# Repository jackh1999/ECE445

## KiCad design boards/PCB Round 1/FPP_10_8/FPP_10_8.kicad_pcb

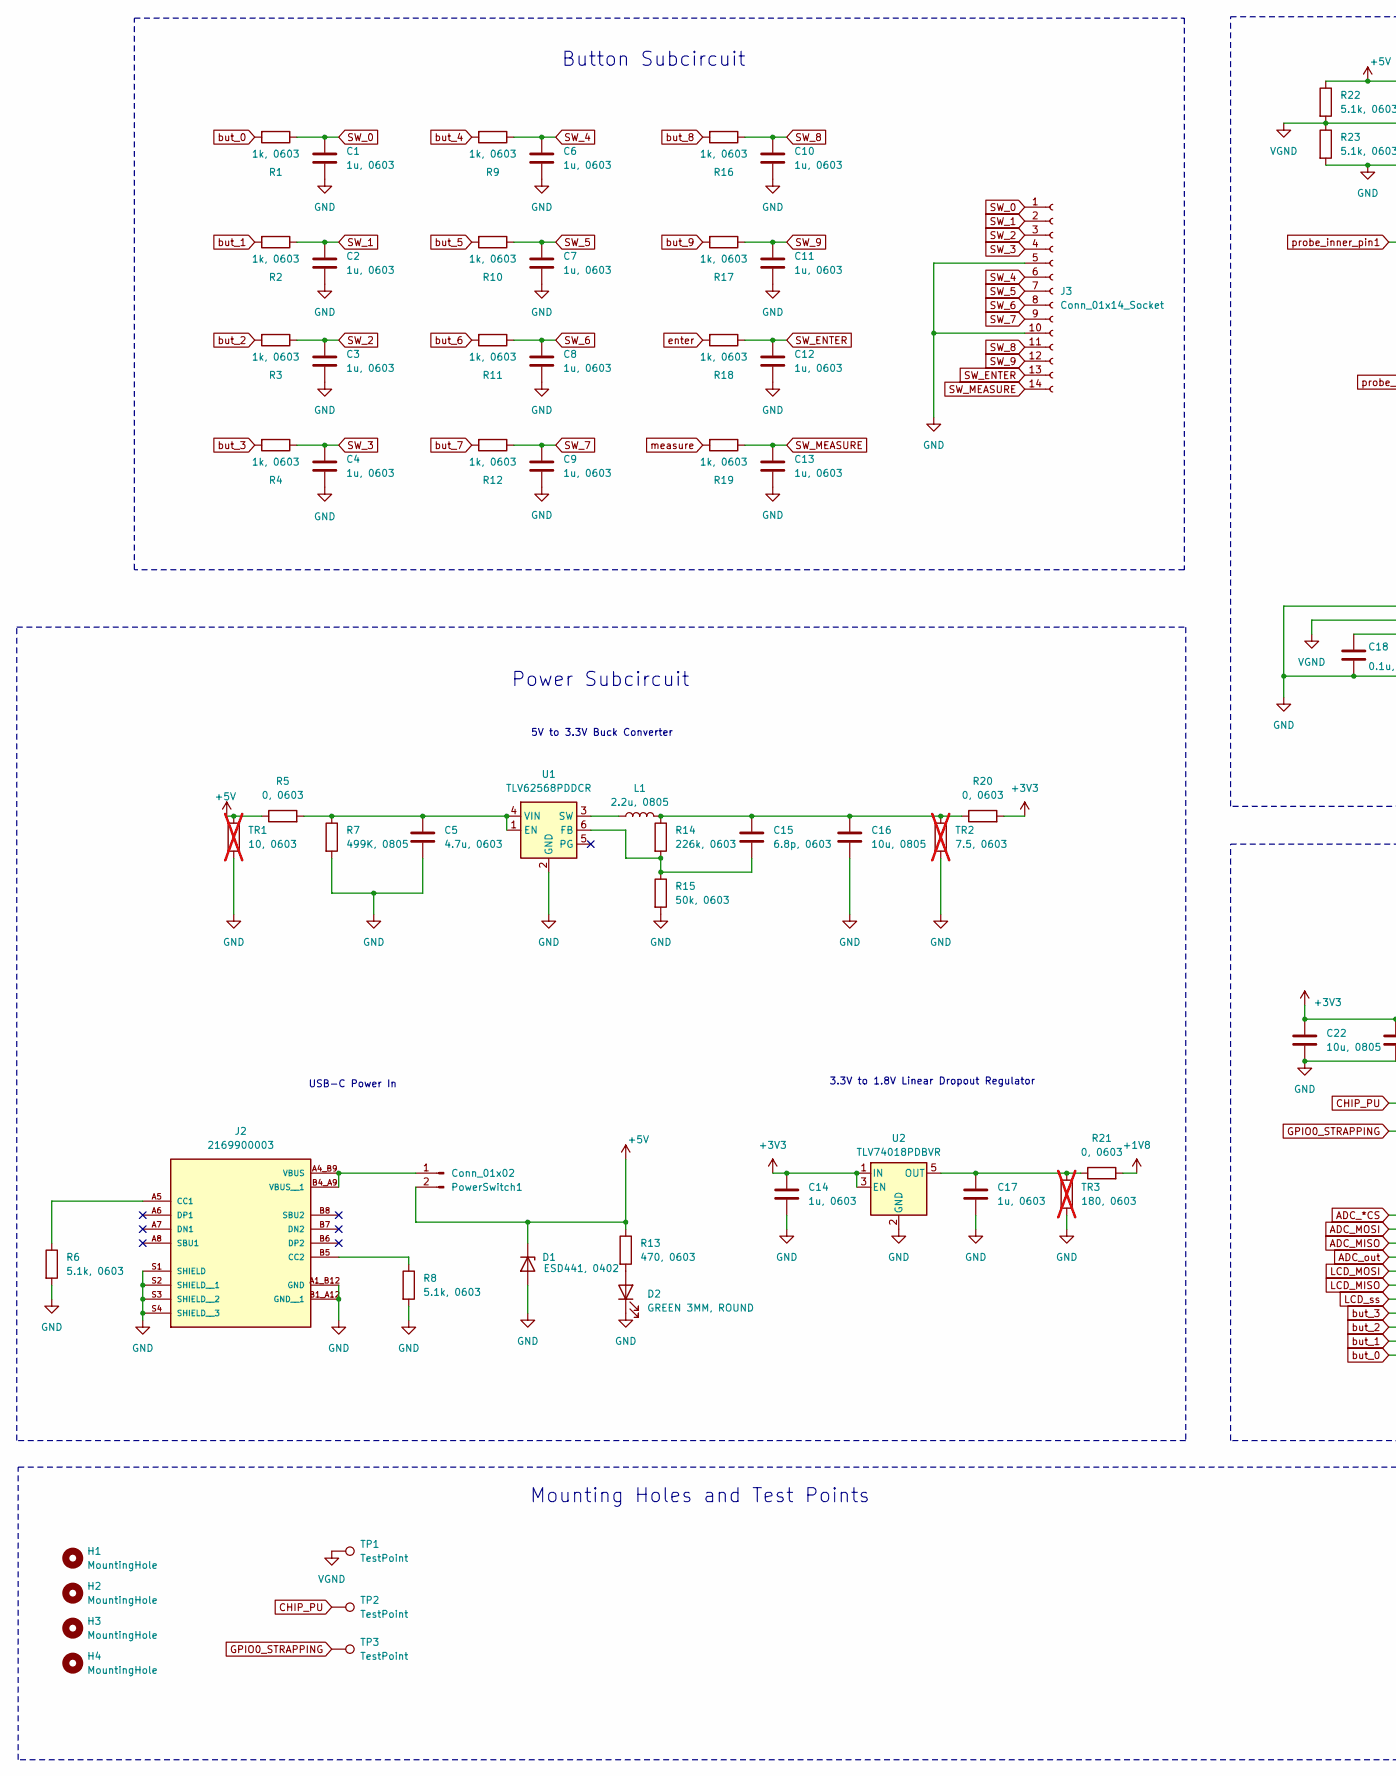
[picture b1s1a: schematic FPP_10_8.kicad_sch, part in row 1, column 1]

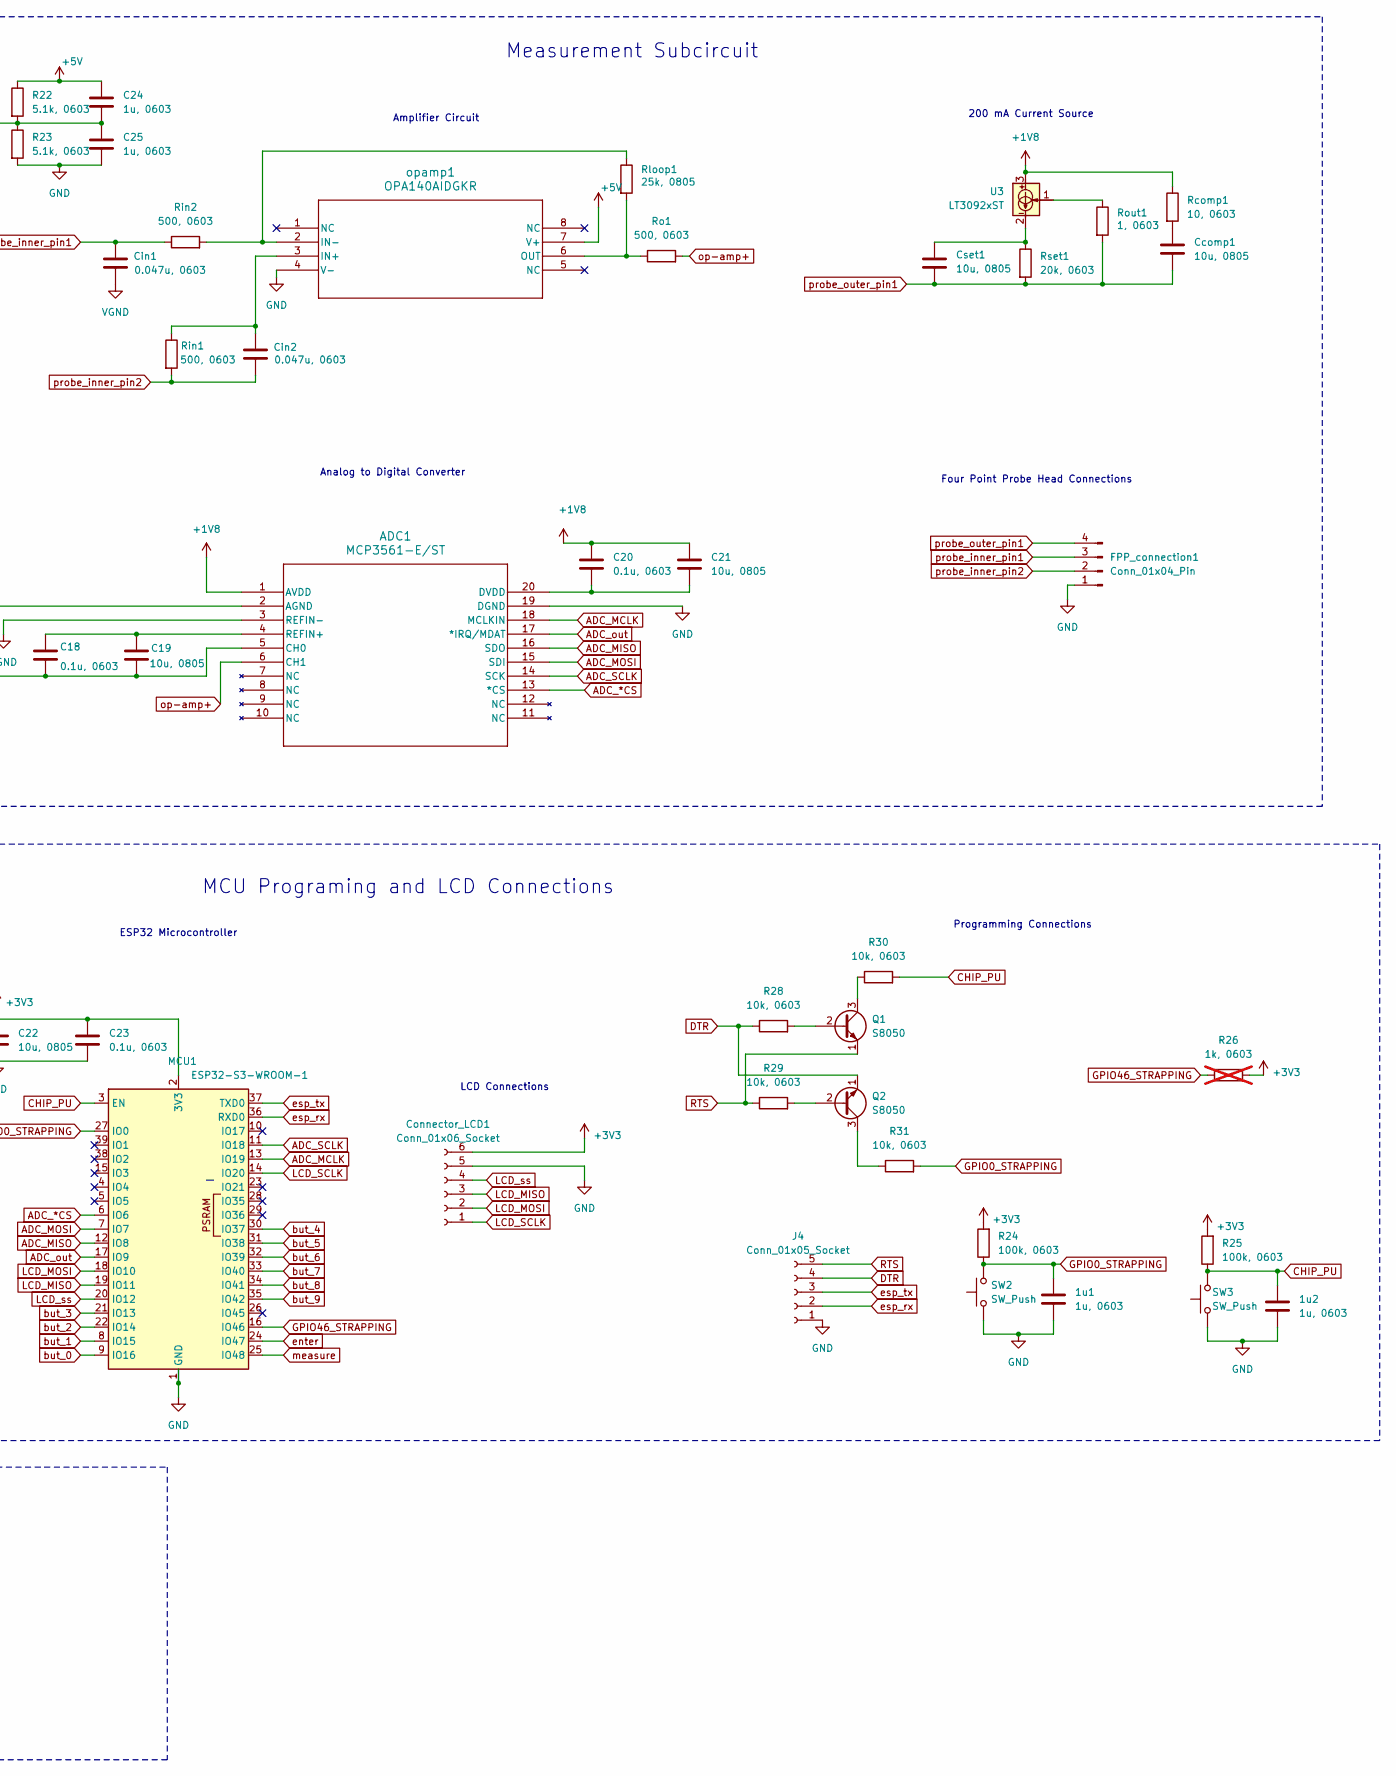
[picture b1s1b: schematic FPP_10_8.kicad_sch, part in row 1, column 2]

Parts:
1u1, 1u2: 1u, 0603; R_0603_1608Metric_Pad0.98x0.95mm_HandSolder
ADC1: MCP3561-E/ST; TSSOP-20_4.4x6.5mm_P0.65mm
C1, C2, C3, C4, C6, C7, C8, C9, C10, C11, C12, C13, C14, C17, C24, C25: 1u, 0603; R_0603_1608Metric_Pad0.98x0.95mm_HandSolder
C5: 4.7u, 0603; R_0603_1608Metric_Pad0.98x0.95mm_HandSolder
C15: 6.8p, 0603; R_0603_1608Metric_Pad0.98x0.95mm_HandSolder
C16, C19, C21, C22: 10u, 0805; R_0805_2012Metric_Pad1.20x1.40mm_HandSolder
C18, C20, C23: 0.1u, 0603; R_0603_1608Metric_Pad0.98x0.95mm_HandSolder
Ccomp1: 10u, 0805; R_0805_2012Metric_Pad1.20x1.40mm_HandSolder
Cin1, Cin2: 0.047u, 0603; R_0603_1608Metric_Pad0.98x0.95mm_HandSolder
Connector_LCD1: Conn_01x06_Socket; PinSocket_1x06_P2.54mm_Vertical
Cset1: 10u, 0805; R_0805_2012Metric_Pad1.20x1.40mm_HandSolder
D1: ESD441, 0402; R_0402_1005Metric_Pad0.72x0.64mm_HandSolder
D2: GREEN 3MM, ROUND; WL-TMRC_3MM
FPP_connection1: Conn_01x04_Pin; PinHeader_1x04_P2.54mm_Vertical
H1, H2, H3, H4: MountingHole; MountingHole_4.3mm_M4
J2: 2169900003; MOLEX_2169900003; PARTREV A1
J3: Conn_01x14_Socket; PinSocket_2x07_P2.54mm_Vertical
J4: Conn_01x05_Socket; PinSocket_1x05_P2.54mm_Vertical
L1: 2.2u, 0805; R_0805_2012Metric_Pad1.20x1.40mm_HandSolder
MCU1: ESP32-S3-WROOM-1
PowerSwitch1: Conn_01x02; Molex_KK-254_AE-6410-02A_1x02_P2.54mm_Vertical
Q1, Q2: S8050; SOT-23-3
R1, R2, R3, R4, R9, R10, R11, R12, R16, R17, R18, R19: 1k, 0603; R_0603_1608Metric_Pad0.98x0.95mm_HandSolder
R5, R20, R21: 0, 0603; R_0603_1608Metric_Pad0.98x0.95mm_HandSolder
R6, R8, R22, R23: 5.1k, 0603; R_0603_1608Metric_Pad0.98x0.95mm_HandSolder
R7: 499K, 0805; R_0805_2012Metric_Pad1.20x1.40mm_HandSolder
R13: 470, 0603; R_0603_1608Metric_Pad0.98x0.95mm_HandSolder
R14: 226k, 0603; R_0603_1608Metric_Pad0.98x0.95mm_HandSolder
R15: 50k, 0603; R_0603_1608Metric_Pad0.98x0.95mm_HandSolder
R24, R25: 100k, 0603; R_0603_1608Metric_Pad0.98x0.95mm_HandSolder
R26: 1k, 0603; R_0603_1608Metric_Pad0.98x0.95mm_HandSolder; not fitted
R28, R29, R30, R31: 10k, 0603; R_0603_1608Metric_Pad0.98x0.95mm_HandSolder
Rcomp1: 10, 0603; R_0603_1608Metric_Pad0.98x0.95mm_HandSolder
Rin1, Rin2: 500, 0603; R_0603_1608Metric_Pad0.98x0.95mm_HandSolder
Rloop1: 25k, 0805; R_0805_2012Metric_Pad1.20x1.40mm_HandSolder
Ro1: 500, 0603; R_0603_1608Metric_Pad0.98x0.95mm_HandSolder
Rout1: 1, 0603; R_0603_1608Metric_Pad0.98x0.95mm_HandSolder
Rset1: 20k, 0603; R_0603_1608Metric_Pad0.98x0.95mm_HandSolder
SW2, SW3: SW_Push; SWITCH_03211B
TP1, TP2, TP3: TestPoint; TestPoint_Pad_1.5x1.5mm
TR1: 10, 0603; R_0603_1608Metric_Pad0.98x0.95mm_HandSolder; not fitted
TR2: 7.5, 0603; R_0603_1608Metric_Pad0.98x0.95mm_HandSolder; not fitted
TR3: 180, 0603; R_0603_1608Metric_Pad0.98x0.95mm_HandSolder; not fitted
U1: TLV62568PDDCR; SOT-23-6
U2: TLV74018PDBVR; SOT-23-5
U3: LT3092xST; SOT-223-3_TabPin2
opamp1: OPA140AIDGKR; DGK8

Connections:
+1V8: ADC1.1 (AVDD), C20.1, C21.1, R21.2, Rcomp1.1, U3.3
+3V3: C14.1, C22.1, C23.1, Connector_LCD1.6, MCU1.2 (3V3), R20.2, R24.2, R25.2, R26.2, U2.1 (IN), U2.3 (EN)
+5V: C24.1, D1.1 (K), PowerSwitch1.2, R5.1, R13.1, R22.1, TR1.2, opamp1.7 (V+)
ADC_*CS: ADC1.13 (*CS), MCU1.6 (IO6)
ADC_MCLK: ADC1.18 (MCLKIN), MCU1.13 (IO19)
ADC_MISO: ADC1.16 (SDO), MCU1.12 (IO8)
ADC_MOSI: ADC1.15 (SDI), MCU1.7 (IO7)
ADC_SCLK: ADC1.14 (SCK), MCU1.11 (IO18)
ADC_out: ADC1.17 (*IRQ/MDAT), MCU1.17 (IO9)
CHIP_PU: 1u2.1, MCU1.3 (EN), R25.1, R30.2, SW3.6, TP2.1
DTR: J4.4, Q2.1 (E), R28.1
GND: 1u1.2, 1u2.2, ADC1.2 (AGND), ADC1.5 (CH0), ADC1.19 (DGND), C1.2, C2.2, C3.2, C4.2, C5.2, C6.2, C7.2, C8.2, C9.2, C10.2, C11.2, C12.2, C13.2, C14.2, C16.2, C17.2, C18.2, C19.2, C22.2, C23.2, C25.2, Connector_LCD1.5, D1.2 (A), D2.1 (K), FPP_connection1.1, J2.A1_B12 (GND), J2.B1_A12 (GND__1), J2.S1 (SHIELD), J2.S2 (SHIELD__1), J2.S3 (SHIELD__2), J2.S4 (SHIELD__3), J3.5, J3.10, J4.1, MCU1.1 (GND), MCU1.40 (GND), MCU1.41 (GND), R6.2, R7.2, R8.2, R15.2, R23.2, SW2.1, SW3.1, TR1.1, TR2.1, TR3.1, U1.2 (GND), U2.2 (GND), opamp1.4 (V-)
GPIO0_STRAPPING: 1u1.1, MCU1.27 (IO0), R24.1, R31.2, SW2.6, TP3.1
GPIO46_STRAPPING: MCU1.16 (IO46), R26.1
LCD_MISO: Connector_LCD1.3, MCU1.19 (IO11)
LCD_MOSI: Connector_LCD1.2, MCU1.18 (IO10)
LCD_SCLK: Connector_LCD1.1, MCU1.14 (IO20)
LCD_ss: Connector_LCD1.4, MCU1.20 (IO12)
unnamed: ADC1.20 (DVDD), C20.2, C21.2
unnamed: ADC1.4 (REFIN+), C18.1, C19.1
unnamed: C15.1, C16.1, L1.2, R14.1, R20.1, TR2.2
unnamed: Ccomp1.1, Rcomp1.2
unnamed: Cset1.1, Rset1.1, U3.2
unnamed: D2.2 (A), R13.2
unnamed: J2.A5 (CC1), R6.1
unnamed: J2.B5 (CC2), R8.1
unnamed: J2.A4_B9 (VBUS), J2.B4_A9 (VBUS__1), PowerSwitch1.1
unnamed: Q1.2 (B), R28.2
unnamed: Q1.3 (C), R30.1
unnamed: Q2.2 (B), R29.2
unnamed: Q2.3 (C), R31.1
unnamed: Rout1.1, U3.1
unnamed: C5.1, R5.2, R7.1, U1.1 (EN), U1.4 (VIN)
unnamed: C15.2, R14.2, R15.1, U1.6 (FB)
unnamed: L1.1, U1.3 (SW)
unnamed: C17.1, R21.1, TR3.2, U2.5 (OUT)
unnamed: Cin2.2, Rin1.1, opamp1.3 (IN+)
unnamed: Rin2.2, Rloop1.1, opamp1.2 (IN-)
unnamed: Rloop1.2, Ro1.1, opamp1.6 (OUT)
RTS: J4.5, Q1.1 (E), R29.1
SW_0: C1.1, J3.1, R1.1
SW_1: C2.1, J3.2, R2.1
SW_2: C3.1, J3.3, R3.1
SW_3: C4.1, J3.4, R4.1
SW_4: C6.1, J3.6, R9.1
SW_5: C7.1, J3.7, R10.1
SW_6: C8.1, J3.8, R11.1
SW_7: C9.1, J3.9, R12.1
SW_8: C10.1, J3.11, R16.1
SW_9: C11.1, J3.12, R17.1
SW_ENTER: C12.1, J3.13, R18.1
SW_MEASURE: C13.1, J3.14, R19.1
VGND: ADC1.3 (REFIN-), C24.2, C25.1, Cin1.1, R22.2, R23.1, TP1.1
but_0: MCU1.9 (IO16), R1.2
but_1: MCU1.8 (IO15), R2.2
but_2: MCU1.22 (IO14), R3.2
but_3: MCU1.21 (IO13), R4.2
but_4: MCU1.30 (IO37), R9.2
but_5: MCU1.31 (IO38), R10.2
but_6: MCU1.32 (IO39), R11.2
but_7: MCU1.33 (IO40), R12.2
but_8: MCU1.34 (IO41), R16.2
but_9: MCU1.35 (IO42), R17.2
enter: MCU1.24 (IO47), R18.2
esp_rx: J4.2, MCU1.36 (RXD0)
esp_tx: J4.3, MCU1.37 (TXD0)
measure: MCU1.25 (IO48), R19.2
op-amp+: ADC1.6 (CH1), Ro1.2
probe_inner_pin1: Cin1.2, FPP_connection1.3, Rin2.1
probe_inner_pin2: Cin2.1, FPP_connection1.2, Rin1.2
probe_outer_pin1: Ccomp1.2, Cset1.2, FPP_connection1.4, Rout1.2, Rset1.2

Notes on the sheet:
USB-C Power In
ESP32 Microcontroller
Amplifier Circuit
3.3V to 1.8V Linear Dropout Regulator
200 mA Current Source
Four Point Probe Head Connections
Measurement Subcircuit
Analog to Digital Converter
Power Subcircuit
Button Subcircuit
LCD Connections
5V to 3.3V Buck Converter
MCU Programing and LCD Connections
Mounting Holes and Test Points
Programming Connections

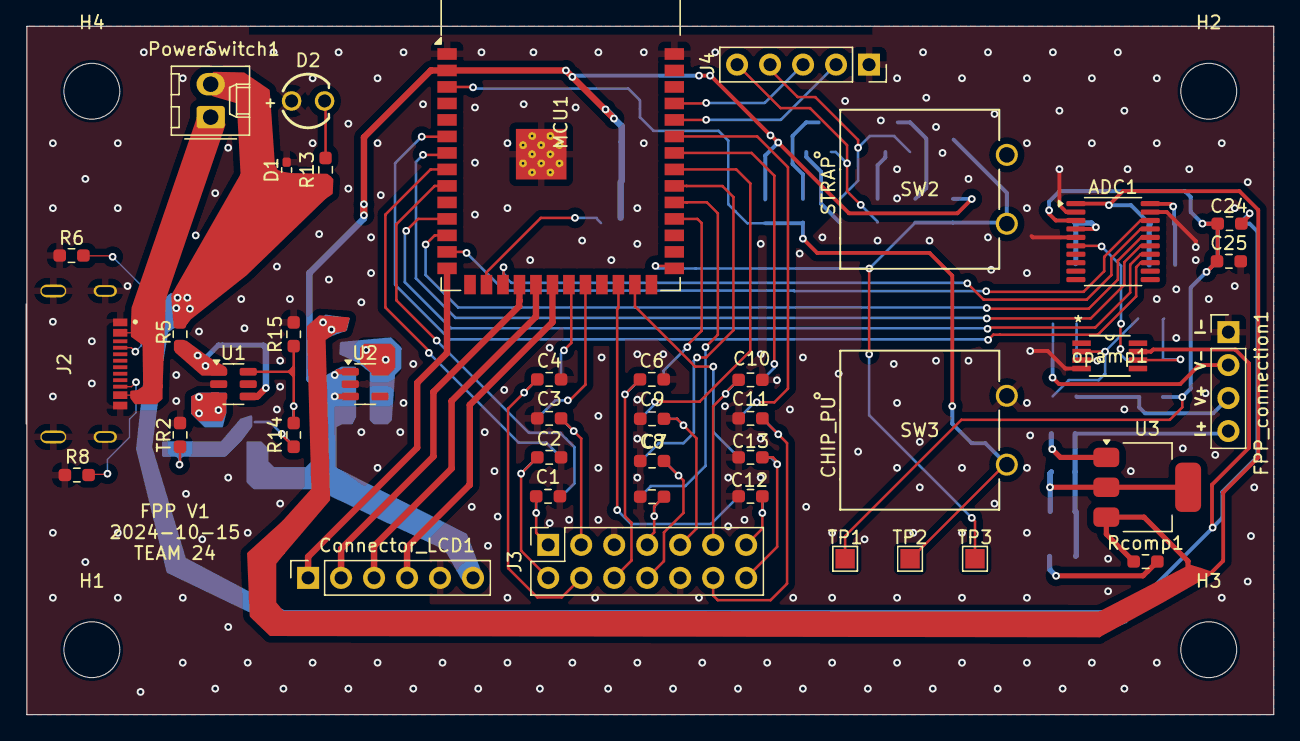
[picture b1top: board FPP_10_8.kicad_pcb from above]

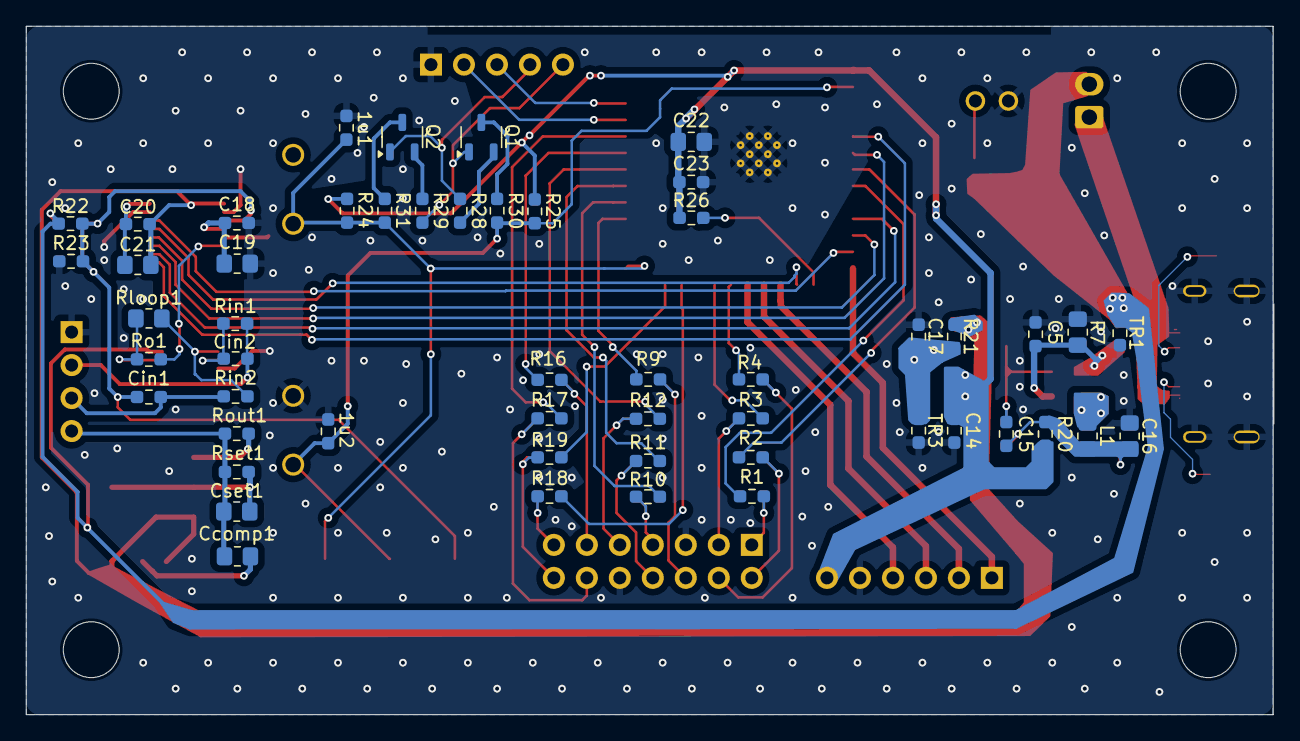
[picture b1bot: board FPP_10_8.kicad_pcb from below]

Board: 2 copper layers, 96.0 x 53.0 mm, 97 parts (52 on the bottom side), 71 nets.

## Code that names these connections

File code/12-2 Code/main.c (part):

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
#define LCD_LED             GPIO_NUM_7
#define LCD_SCK             GPIO_NUM_20
#define LCD_MOSI            GPIO_NUM_10
#define LCD_DC              GPIO_NUM_11
#define LCD_RESET           GPIO_NUM_42
#define LCD_CS              GPIO_NUM_12

#define ADC_SCK             GPIO_NUM_18
#define ADC_MCK             GPIO_NUM_19
#define ADC_MOSI            GPIO_NUM_7
#define ADC_MISO            GPIO_NUM_8
#define ADC_CS              GPIO_NUM_6
#define ADC_OUT             GPIO_NUM_9

#define LCD_PARALLEL        8
#define LCD_H_RES           240
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
    //GPIO_BUTTON_0 = DOWN; PIN 16
    //GPIO_BUTTON_1 = UP; PIN 15
    //GPIO_BUTTON_2 = ENTER; PIN 14
    //GPIO_BUTTON_3 = MEASURE; PIN
    

    while(true){
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
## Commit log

2024-09-16 Create README.md
    a
2024-09-16 Create boards file
2024-09-16 Create code folder
2024-09-16 Create models folder
2024-09-16 Rename Block Diagram.pdf to BlockDiagram.pdf
2024-09-16 Rename Block Diagram.jpg to BlockDiagram.jpg
2024-10-08 Create Design Document (10-4)
2024-10-08 Update README.md
    add some subsystem description
2024-12-03 Create Final Code
2024-12-05 Update README.md
    Printing Stuff
